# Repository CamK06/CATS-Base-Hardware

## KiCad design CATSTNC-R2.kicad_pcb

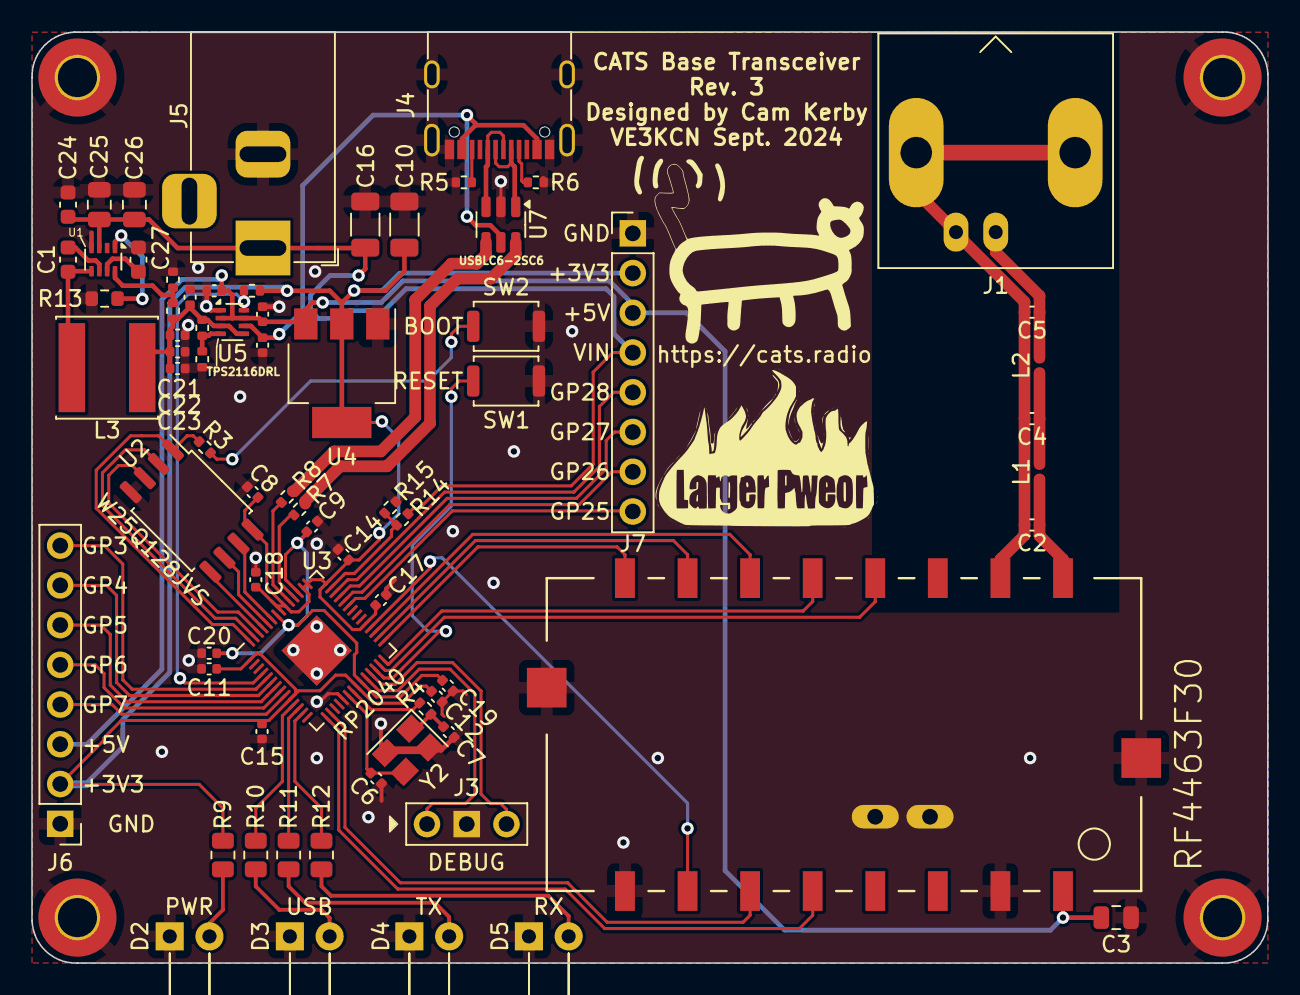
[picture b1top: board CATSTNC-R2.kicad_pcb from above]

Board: 2 copper layers, 79.0 x 59.5 mm, 75 parts (0 on the bottom side), 64 nets.

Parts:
C1, C24: 100nF; C_0603_1608Metric
C2, C5: 7.5pF; C_0402_1005Metric
C3: 4.7uF; C_0805_2012Metric
C4: 13pF; C_0402_1005Metric
C6, C7: 27pF; C_0402_1005Metric
C8, C12, C14, C15, C17, C19, C20, C23: 100nF; C_0402_1005Metric
C9, C11, C18: 1uF; C_0402_1005Metric
C10, C16: 4.7uF; C_1206_3216Metric
C13, C28, C29, C30: 10uF; C_0402_1005Metric
C21, C22: 22uF; C_0402_1005Metric
C25, C26: 10uF; C_0805_2012Metric
C27: 33nF; C_0603_1608Metric
D2, D3, D4, D5: LED; LED_D3.0mm_Horizontal_O6.35mm_Z6.0mm
H1, H2, H3, H4: MountingHole_2.5mm_Pad_TopBottom
J1: BNC; BNC_Amphenol_B6252HB-NPP3G-50_Horizontal
J3: DEBUG; PinHeader_1x03_P2.54mm_Vertical
J4: USB_C_Receptacle_USB2.0; USB_C_Receptacle_G-Switch_GT-USB-7010ASV
J5: DC IN; BarrelJack_Horizontal
J6: GPIO-1; PinHeader_1x08_P2.54mm_Vertical
J7: GPIO-2; PinHeader_1x08_P2.54mm_Vertical
L1, L2: 24nH; L_0402_1005Metric
L3: 6.8uH; L_Sunlord_SWPA6020S
R1, R14, R17: 54.9K 1%; R_0402_1005Metric
R2, R15: 10.0K 1%; R_0402_1005Metric
R3: 1K; R_0402_1005Metric
R4: 1k; R_0402_1005Metric
R5, R6: 5.11K; R_0402_1005Metric
R7, R8: 27 or 22; R_0402_1005Metric
R9, R10, R11, R12: 220; R_0805_2012Metric
R13: 0; R_0603_1608Metric
R18: 15.0K 1%; R_0402_1005Metric
R19: 10K; R_0402_1005Metric
SW1: RESET; SW_Push_SPST_NO_Alps_SKRK
SW2: BOOT; SW_Push_SPST_NO_Alps_SKRK
U1: TPS62933; SOT-583-8
U2: W25Q128JVS; SOIC-8_5.23x5.23mm_P1.27mm
U3: RP2040; QFN-56-1EP_7x7mm_P0.4mm_EP3.2x3.2mm
U4: NCP1117-3.3_SOT223; SOT-223-3_TabPin2
U5: TPS2116DRL; SOT-583-8
U6: RF4463F30
U7: USBLC6-2SC6; SOT-23-6
Y2: C9002; Crystal_SMD_3225-4Pin_3.2x2.5mm

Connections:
+1V1: C9.1, C19.1, C20.1, U3.23 (DVDD), U3.45 (VREG_VOUT), U3.50 (DVDD)
+3V3: C8.1, C10.1, C11.1, C12.1, C14.1, C15.1, C17.1, C18.1, J6.2, J7.2, R9.2, R19.2, U2.8 (VCC), U3.1 (IOVDD), U3.10 (IOVDD), U3.22 (IOVDD), U3.33 (IOVDD), U3.42 (IOVDD), U3.43 (ADC_AVDD), U3.44 (VREG_IN), U3.48 (USB_VDD), U3.49 (IOVDD), U4.2 (VO)
+5V: C3.1, C29.1, C30.1, J6.3, J7.3, U4.3 (VI), U5.2 (VOUT), U5.7 (VOUT), U6.1 (VCC)
D+: R8.2, U7.4 (I/O2)
D-: R7.2, U7.6 (I/O1)
GND: C3.2, C6.2, C7.2, C8.2, C9.2, C10.2, C11.2, C12.2, C13.2, C14.2, C15.2, C16.2, C17.2, C18.2, C19.2, C20.2, C21.2, C22.2, C23.2, C24.2, C25.2, C26.2, C27.2, C28.2, C29.2, C30.2, D2.1 (K), D3.1 (K), D4.1 (K), D5.1 (K), H1.1, H2.1, H3.1, H4.1, J3.2, J4.A1 (GND), J4.A12 (GND), J4.B1 (GND), J4.B12 (GND), J4.S1 (SHIELD), J5.2, J6.1, J7.1, R2.2, R5.2, R6.1, R13.2, R15.2, R18.1, SW1.1, SW2.1, U1.4 (GND), U2.4 (GND), U3.19 (TESTEN), U3.57 (GND), U4.1 (GND), U5.1 (GND), U6.2 (GND), U6.8 (GND), U6.SHLD_1, U6.SHLD_2, U6.SHLD_3, U6.SHLD_4, U7.2 (GND), Y2.2, Y2.4
GNDA: C2.2, C4.2, C5.2, J1.2 (Ext), U6.15 (GND)
GP3: J6.8, U3.5 (GPIO3)
GP4: J6.7, U3.6 (GPIO4)
GP5: J6.6, U3.7 (GPIO5)
GP6: J6.5, U3.8 (GPIO6)
GP7: J6.4, U3.9 (GPIO7)
GP25: J7.8, U3.37 (GPIO25)
GP26: J7.7, U3.38 (GPIO26_ADC0)
GP27: J7.6, U3.39 (GPIO27_ADC1)
GP28: J7.5, U3.40 (GPIO28_ADC2)
IRQ: U3.16 (GPIO13), U6.6 (IRQ)
MUX_ST: R19.1, U3.4 (GPIO2), U5.8 (ST)
unnamed: C4.1, L1.2, L2.1
unnamed: C7.1, R4.2, Y2.1
unnamed: D2.2 (A), R9.1
unnamed: D3.2 (A), R10.1
unnamed: D4.2 (A), R11.1
unnamed: D5.2 (A), R12.1
unnamed: C5.1, J1.1 (In), L2.2
unnamed: J4.A5 (CC1), R6.2
unnamed: J4.B5 (CC2), R5.1
unnamed: J4.A6 (D+), J4.B6 (D+), U7.3 (I/O2)
unnamed: J4.A7 (D-), J4.B7 (D-), U7.1 (I/O1)
unnamed: R3.1, SW2.2
unnamed: C1.1, U1.6 (BST)
unnamed: C27.1, U1.7 (SS)
unnamed: C1.2, L3.1, U1.5 (SW)
unnamed: SW1.2, U3.26 (RUN)
unnamed: R7.1, U3.46 (USB_DM)
unnamed: R8.1, U3.47 (USB_DP)
unnamed: C6.1, U3.20 (XIN), Y2.3
unnamed: R4.1, U3.21 (XOUT)
unnamed: R17.1, R18.2, U5.4 (PR1)
unnamed: C2.1, L1.1, U6.16 (ANT)
QSPI_CLK: U2.6 (CLK), U3.52 (QSPI_SCLK)
QSPI_SD0: U2.5 (DI(IO0)), U3.53 (QSPI_SD0)
QSPI_SD1: U2.2 (DO(IO1)), U3.55 (QSPI_SD1)
QSPI_SD2: U2.3 (IO2), U3.54 (QSPI_SD2)
QSPI_SD3: U2.7 (IO3), U3.51 (QSPI_SD3)
QSPI_SS: R3.2, U2.1 (~CS), U3.56 (QSPI_SS)
REG_5V: C13.1, C21.1, C22.1, C23.1, L3.2, R1.1, R17.2, U5.3 (VIN1), U5.5 (MODE)
RFGP0: U3.27 (GPIO16), U6.13 (GPIO0)
RFGP1: U3.28 (GPIO17), U6.12 (GPIO1)
RT: R13.1, U1.1 (RT)
RX_LED: R12.2, U3.13 (GPIO10)
SDN: U3.15 (GPIO12), U6.5 (SDN)
SPI0_CSN: U3.32 (GPIO21), U6.7 (SEL)
SPI0_RX: U3.31 (GPIO20), U6.11 (SDO)
SPI0_SCK: U3.29 (GPIO18), U6.9 (SCLK)
SPI0_TX: U3.30 (GPIO19), U6.10 (SDI)
SWCLK: J3.1, U3.24 (SWCLK)
SWD: J3.3, U3.25 (SWD)
TX_LED: R11.2, U3.12 (GPIO9)
USB_LED: R10.2, U3.11 (GPIO8)
USB_VBUS: C28.1, J4.A4 (VBUS), J4.A9 (VBUS), J4.B4 (VBUS), J4.B9 (VBUS), U5.6 (VIN2), U7.5 (VBUS)
VCC: C16.1, C24.1, C25.1, C26.1, J5.1, J7.4, R14.1, U1.3 (VIN)
VCC_VOLTS: R14.2, R15.1, U3.41 (GPIO29_ADC3)
VFB: R1.2, R2.1, U1.8 (FB)

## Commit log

2023-11-28 Add readme
2023-11-29 Improve design
2023-12-02 More work
2023-12-05 Rev 2 Ordered
2024-09-26 Start work on Rev 3
2024-09-27 More work on Rev 3
2024-09-27 Rev 3
2024-09-27 Remove BAT54C
2024-09-27 Add power mux, USB TVS
2024-09-27 JLC part selection
2024-09-28 Add SWD header, VCC voltmeter, replace GP29 with VIN
2024-10-06 Did some stuff idk
2024-10-06 BOOT silkscreen text alignment was bothering me
2024-10-06 Made some small optimizations: see full commit message.
    * Changed PCB text font to Liberation Sans
    * Re-added semiconductor part values to front silkscreen
    * Moved GPIO header closer to edge of board, per general practice
    * Moved some existing silkscreen messages
